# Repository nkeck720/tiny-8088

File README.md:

# tiny-8088
The Tiny 8088 KiCAD files. This exists as a mirror only. If you have issues with the board, email me at noahkeck72@gmail.com with
the subject line "8088".

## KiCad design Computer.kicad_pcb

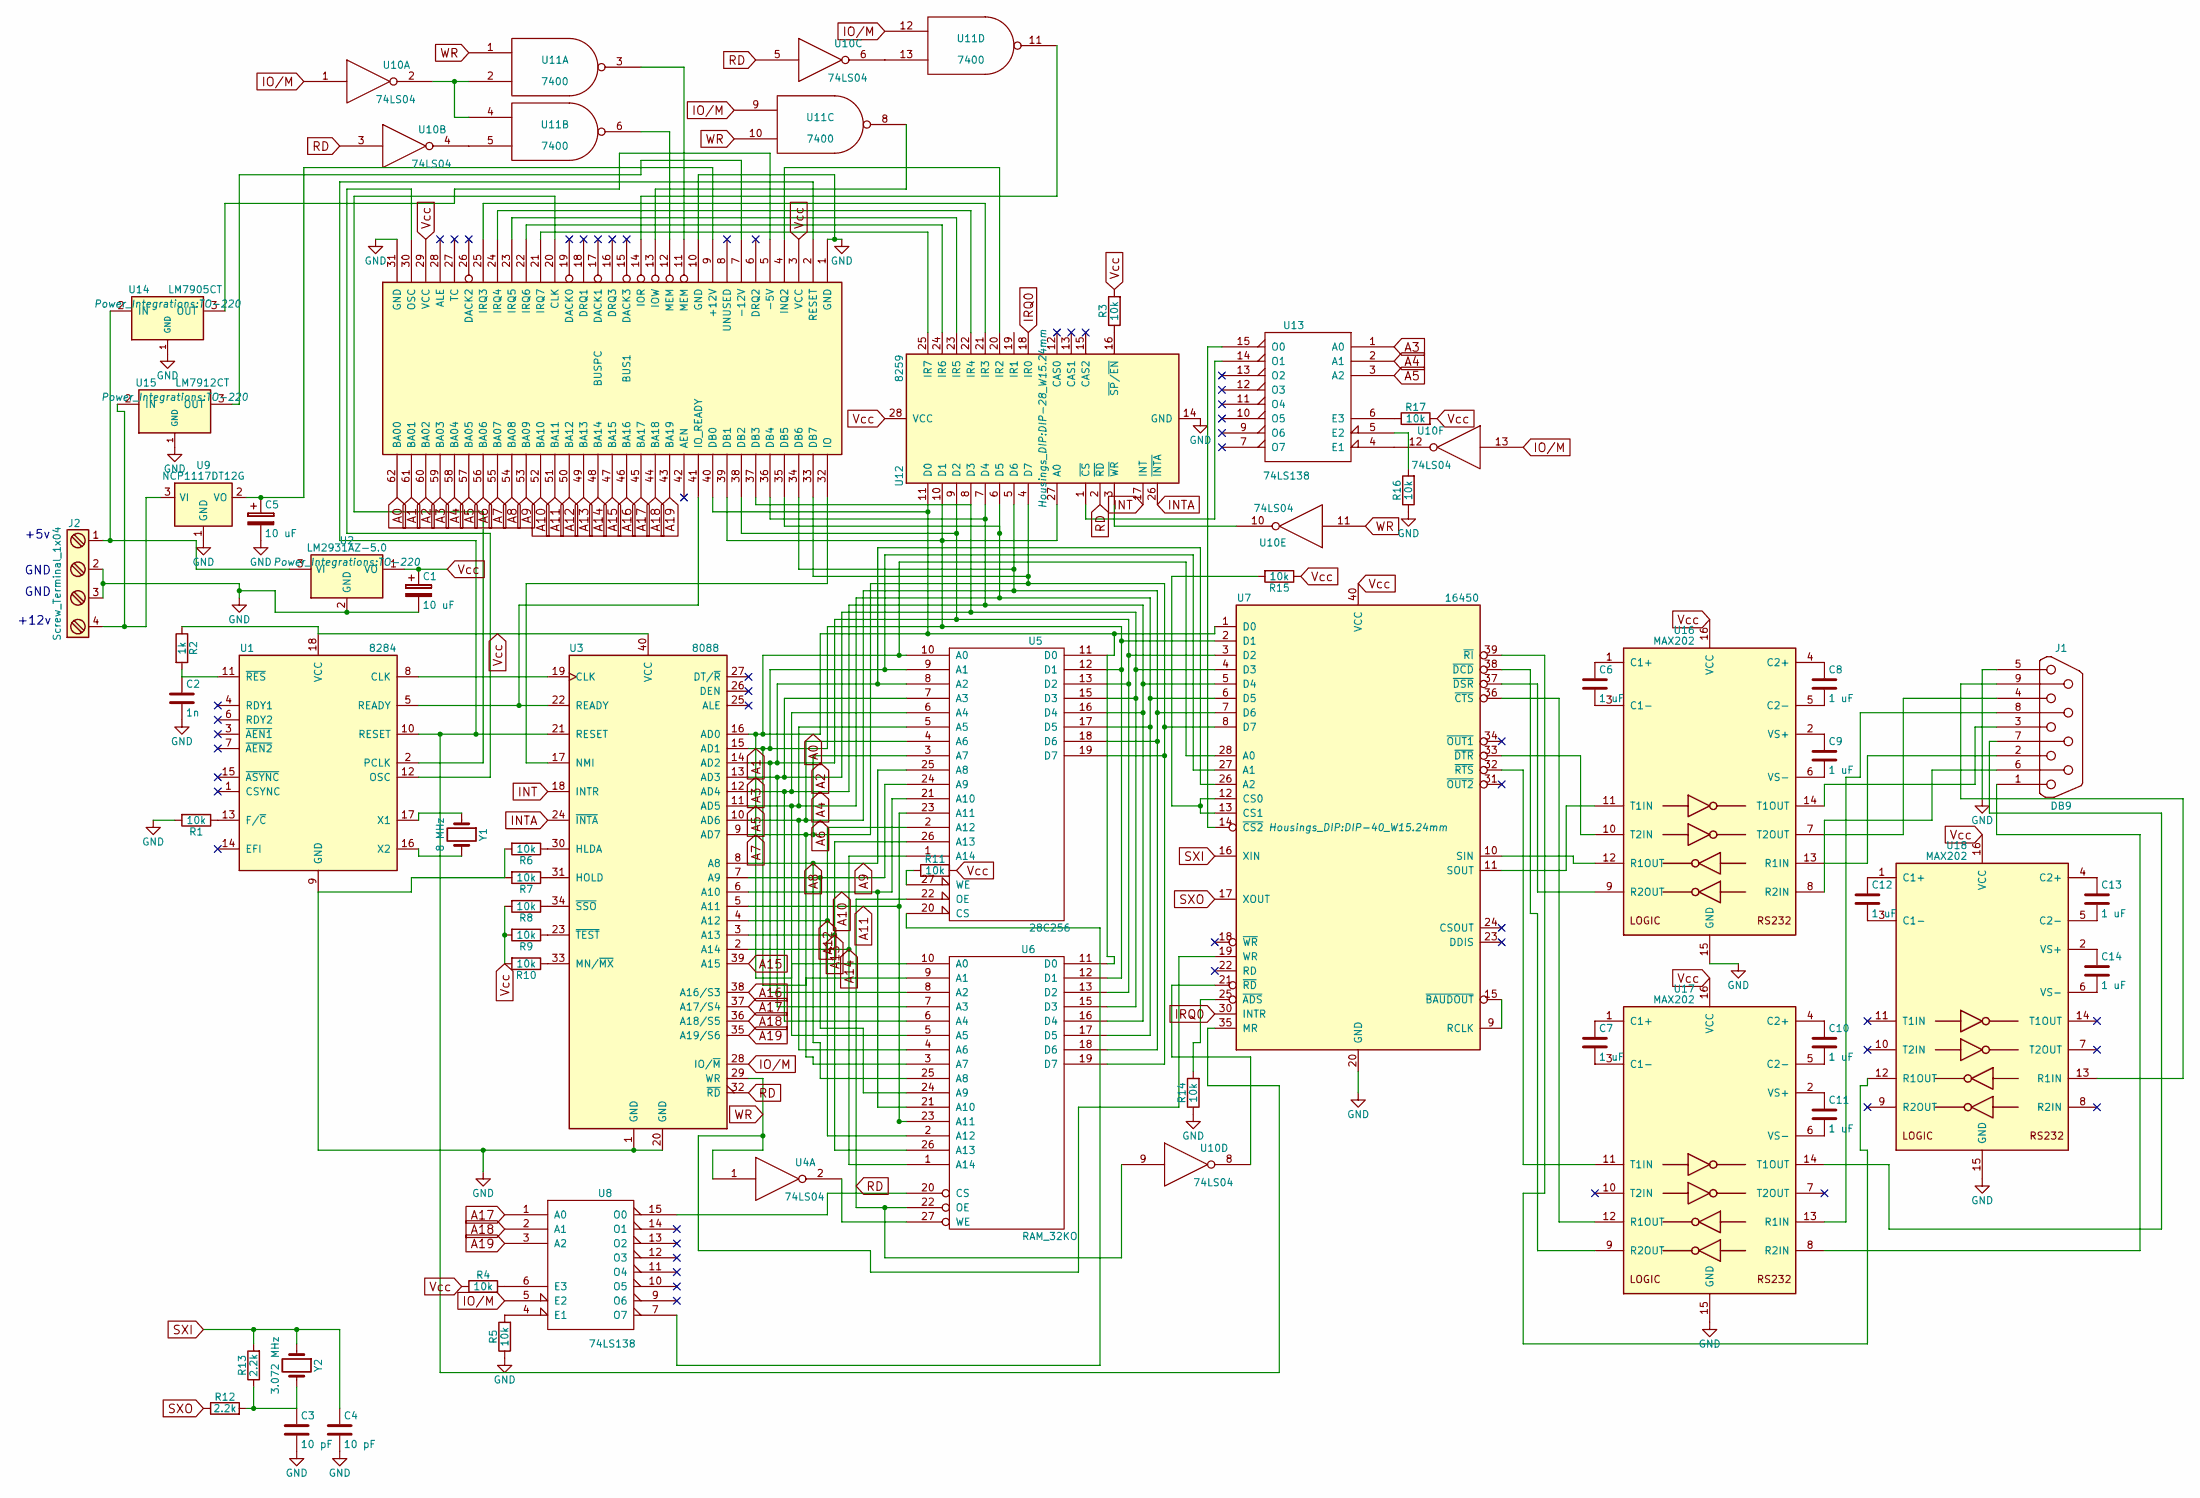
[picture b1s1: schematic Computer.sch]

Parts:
BUS1: BUSPC; ISA8
C1, C5: 10 uF; CP_Radial_D8.0mm_P3.80mm
C2: 1n; C_0603_HandSoldering
C3, C4: 10 pF; C_0603_HandSoldering
C6, C7, C8, C9, C10, C11, C12, C13, C14: 1 uF; C_0603_HandSoldering
J1: DB9; DB9FC
J2: Screw_Terminal_1x04; TerminalBlock_Pheonix_MKDS1.5-4pol
R1, R3, R4, R5, R6, R7, R8, R9, R10, R11, R14, R15, R16, R17: 10k; R_Axial_DIN0204_L3.6mm_D1.6mm_P7.62mm_Horizontal
R2: 1k; R_Axial_DIN0204_L3.6mm_D1.6mm_P7.62mm_Horizontal
R12, R13: 2.2k; R_Axial_DIN0204_L3.6mm_D1.6mm_P7.62mm_Horizontal
U1: 8284; DIP-18_W7.62mm
U2: LM2931AZ-5.0; TO-220
U3: 8088; DIP-40_W15.24mm
U4, U10: 74LS04; DIP-14_W7.62mm
U5: 28C256; DIP-28_W7.62mm
U6: RAM_32KO; DIP-28_W7.62mm
U7: 16450; DIP-40_W15.24mm
U8, U13: 74LS138; DIP-16_W7.62mm
U9: NCP1117DT12G; TO-220
U11: 7400; DIP-14_W7.62mm
U12: 8259; DIP-28_W15.24mm
U14: LM7905CT; TO-220
U15: LM7912CT; TO-220
U16, U17, U18: MAX202; DIP-16_W7.62mm
Y1: 8 MHz; Crystal_SMD_FOX_FE-2pin_7.5x5.0mm
Y2: 3.072 MHz; Crystal_SMD_FOX_FE-2pin_7.5x5.0mm

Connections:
A0: BUS1.33 (DB7), BUS1.35 (DB5), BUS1.37 (DB3), BUS1.39 (DB1), BUS1.40 (DB0), BUS1.55 (BA07), BUS1.57 (BA05), BUS1.59 (BA03), BUS1.61 (BA01), BUS1.62 (BA00), U3.9 (AD7), U3.11 (AD5), U3.13 (AD3), U3.15 (AD1), U3.16 (AD0), U5.3 (A7), U5.5 (A5), U5.7 (A3), U5.9 (A1), U5.10 (A0), U5.11 (D0), U5.12 (D1), U5.15 (D3), U5.17 (D5), U5.19 (D7), U6.3 (A7), U6.5 (A5), U6.7 (A3), U6.9 (A1), U6.10 (A0), U6.11 (D0), U6.12 (D1), U6.15 (D3), U6.17 (D5), U6.19 (D7), U7.1 (D0), U7.2 (D1), U7.4 (D3), U7.6 (D5), U7.8 (D7), U7.27 (A1), U7.28 (A0), U12.4 (D7), U12.6 (D5), U12.8 (D3), U12.10 (D1), U12.11 (D0), U12.27 (A0), U13.1 (A0), U13.3 (A2)
A2: BUS1.38 (DB2), BUS1.60 (BA02), U3.14 (AD2), U5.8 (A2), U5.13 (D2), U6.8 (A2), U6.13 (D2), U7.3 (D2), U7.26 (A2), U12.9 (D2)
A4: BUS1.36 (DB4), BUS1.58 (BA04), U3.12 (AD4), U5.6 (A4), U5.16 (D4), U6.6 (A4), U6.16 (D4), U7.5 (D4), U12.7 (D4), U13.2 (A1)
A6: BUS1.34 (DB6), BUS1.56 (BA06), U3.10 (AD6), U5.4 (A6), U5.18 (D6), U6.4 (A6), U6.18 (D6), U7.7 (D6), U12.5 (D6)
A8: BUS1.53 (BA09), BUS1.54 (BA08), U3.8 (A8), U5.25 (A8), U6.25 (A8)
A10: BUS1.52 (BA10), U3.6 (A10), U5.21 (A10), U6.21 (A10)
A11: BUS1.51 (BA11), U3.5 (A11), U5.23 (A11), U6.23 (A11)
A12: BUS1.50 (BA12), U3.4 (A12), U5.2 (A12), U6.2 (A12)
A13: BUS1.49 (BA13), U3.3 (A13), U5.26 (A13), U6.26 (A13)
A14: BUS1.48 (BA14), U3.2 (A14), U5.1 (A14), U6.1 (A14)
A15: BUS1.47 (BA15), U3.39 (A15)
A16: BUS1.46 (BA16), U3.38 (A16/S3)
A17: BUS1.45 (BA17), U3.37 (A17/S4), U8.1 (A0)
A18: BUS1.44 (BA18), U3.36 (A18/S5), U8.2 (A1)
A19: BUS1.43 (BA19), U3.35 (A19/S6), U8.3 (A2)
INT: U3.18 (INTR), U12.17 (INT)
INTA: U3.24 (~INTA~), U12.26 (~INTA~)
IO/M: U3.28 (IO/~M~), U8.5 (E2), U10.1, U10.13, U11.9, U11.12
IRQ0: U7.30 (INTR), U12.18 (IR0)
unnamed: BUS1.2 (RESET), U1.10 (RESET), U3.21 (RESET), U7.35 (MR)
unnamed: BUS1.4 (INQ2), U12.20 (IR2)
unnamed: BUS1.5 (-5V), U14.3 (OUT)
unnamed: BUS1.7 (-12V), U15.3 (OUT)
unnamed: BUS1.9 (+12V), C5.1, U9.2 (VO)
unnamed: BUS1.11 (MEM), U11.3
unnamed: BUS1.12 (MEM), U11.6
unnamed: BUS1.13 (IOW), U11.8
unnamed: BUS1.14 (IOR), U11.11
unnamed: BUS1.20 (CLK), U1.2 (PCLK)
unnamed: BUS1.21 (IRQ7), U12.25 (IR7)
unnamed: BUS1.22 (IRQ6), U12.24 (IR6)
unnamed: BUS1.23 (IRQ5), U12.23 (IR5)
unnamed: BUS1.24 (IRQ4), U12.22 (IR4)
unnamed: BUS1.25 (IRQ3), U12.21 (IR3)
unnamed: BUS1.30 (OSC), U1.12 (OSC)
unnamed: BUS1.32 (IO), U3.17 (NMI)
unnamed: BUS1.41 (IO_READY), U1.5 (READY), U3.22 (READY)
unnamed: C2.1, R2.2, U1.11 (~RES~)
unnamed: C3.1, R12.2, R13.1, Y2.2
unnamed: C6.1, U16.1 (C1+)
unnamed: C6.2, U16.3 (C1-)
unnamed: C7.1, U17.1 (C1+)
unnamed: C7.2, U17.3 (C1-)
unnamed: C8.1, U16.4 (C2+)
unnamed: C8.2, U16.5 (C2-)
unnamed: C9.1, U16.2 (VS+)
unnamed: C9.2, U16.6 (VS-)
unnamed: C10.1, U17.4 (C2+)
unnamed: C10.2, U17.5 (C2-)
unnamed: C11.1, U17.2 (VS+)
unnamed: C11.2, U17.6 (VS-)
unnamed: C12.1, U18.1 (C1+)
unnamed: C12.2, U18.3 (C1-)
unnamed: C13.1, U18.4 (C2+)
unnamed: C13.2, U18.5 (C2-)
unnamed: C14.1, U18.2 (VS+)
unnamed: C14.2, U18.6 (VS-)
unnamed: J1.1, U17.8 (R2IN)
unnamed: J1.2, U16.13 (R1IN)
unnamed: J1.3, U16.14 (T1OUT)
unnamed: J1.4, U16.7 (T2OUT)
unnamed: J1.6, U16.8 (R2IN)
unnamed: J1.7, U17.14 (T1OUT)
unnamed: J1.8, U17.13 (R1IN)
unnamed: J2.1, U2.3 (VI), U14.2 (IN)
unnamed: J2.4, U9.3 (VI), U15.2 (IN)
unnamed: R1.1, U1.13 (F/~C~)
unnamed: R3.1, U12.16 (~SP~/~EN~)
unnamed: R4.2, U8.6 (E3)
unnamed: R5.2, U8.4 (E1)
unnamed: R6.1, U3.30 (HLDA)
unnamed: R7.1, U3.31 (HOLD)
unnamed: R8.1, U3.34 (~SSO~)
unnamed: R9.1, U3.23 (~TEST~)
unnamed: R10.1, U3.33 (MN/~MX~)
unnamed: R11.1, U5.27 (WE)
unnamed: R14.2, U7.25 (~ADS~)
unnamed: R15.2, U7.12 (CS0), U7.13 (CS1)
unnamed: R16.2, U13.5 (E2)
unnamed: R17.1, U13.6 (E3)
unnamed: U1.8 (CLK), U3.19 (CLK)
unnamed: U1.16 (X2), Y1.2
unnamed: U1.17 (X1), Y1.1
unnamed: U3.7 (A9), U5.24 (A9), U6.24 (A9)
unnamed: U4.2, U6.27 (WE)
unnamed: U5.20 (CS), U8.7 (O7)
unnamed: U6.20 (CS), U8.15 (O0)
unnamed: U7.9 (RCLK), U7.15 (~BAUDOUT~)
unnamed: U10.2, U11.2, U11.4
unnamed: U10.4, U11.5
unnamed: U10.6, U11.13
unnamed: U7.21 (~RD~), U10.8
unnamed: U10.10, U12.3 (~WR~)
unnamed: U10.12, U13.4 (E1)
unnamed: U12.1 (~CS~), U13.14 (O1)
unnamed: U7.14 (~CS2~), U13.15 (O0)
unnamed: U7.37 (~DSR~), U16.9 (R2OUT)
unnamed: U7.33 (~DTR~), U16.10 (T2IN)
unnamed: U7.11 (SOUT), U16.11 (T1IN)
unnamed: U7.10 (SIN), U16.12 (R1OUT)
unnamed: U7.38 (~DCD~), U17.9 (R2OUT)
unnamed: U7.32 (~RTS~), U17.11 (T1IN)
unnamed: U7.36 (~CTS~), U17.12 (R1OUT)
unnamed: U7.39 (~RI~), U18.12 (R1OUT)
RD: U3.32 (~RD~), U5.22 (OE), U6.22 (OE), U10.3, U10.5, U10.9, U12.2 (~RD~)
SXI: C4.1, R13.2, U7.16 (XIN), Y2.1
SXO: R12.1, U7.17 (XOUT)
Vcc: BUS1.3 (VCC), BUS1.29 (VCC), C1.1, R2.1, R3.2, R4.1, R8.2, R9.2, R10.2, R11.2, R15.1, R17.2, U1.18 (VCC), U2.1 (VO), U3.40 (VCC), U4.14 (VCC), U5.28 (VCC), U6.28 (VCC), U7.40 (VCC), U8.16 (VCC), U10.14 (VCC), U11.14 (VCC), U12.28 (VCC), U13.16 (VCC), U16.16 (VCC), U17.16 (VCC), U18.16 (VCC)
WR: U3.29 (WR), U4.1, U7.19 (WR), U10.11, U11.1, U11.10

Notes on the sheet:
+5v
GND
+12v

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
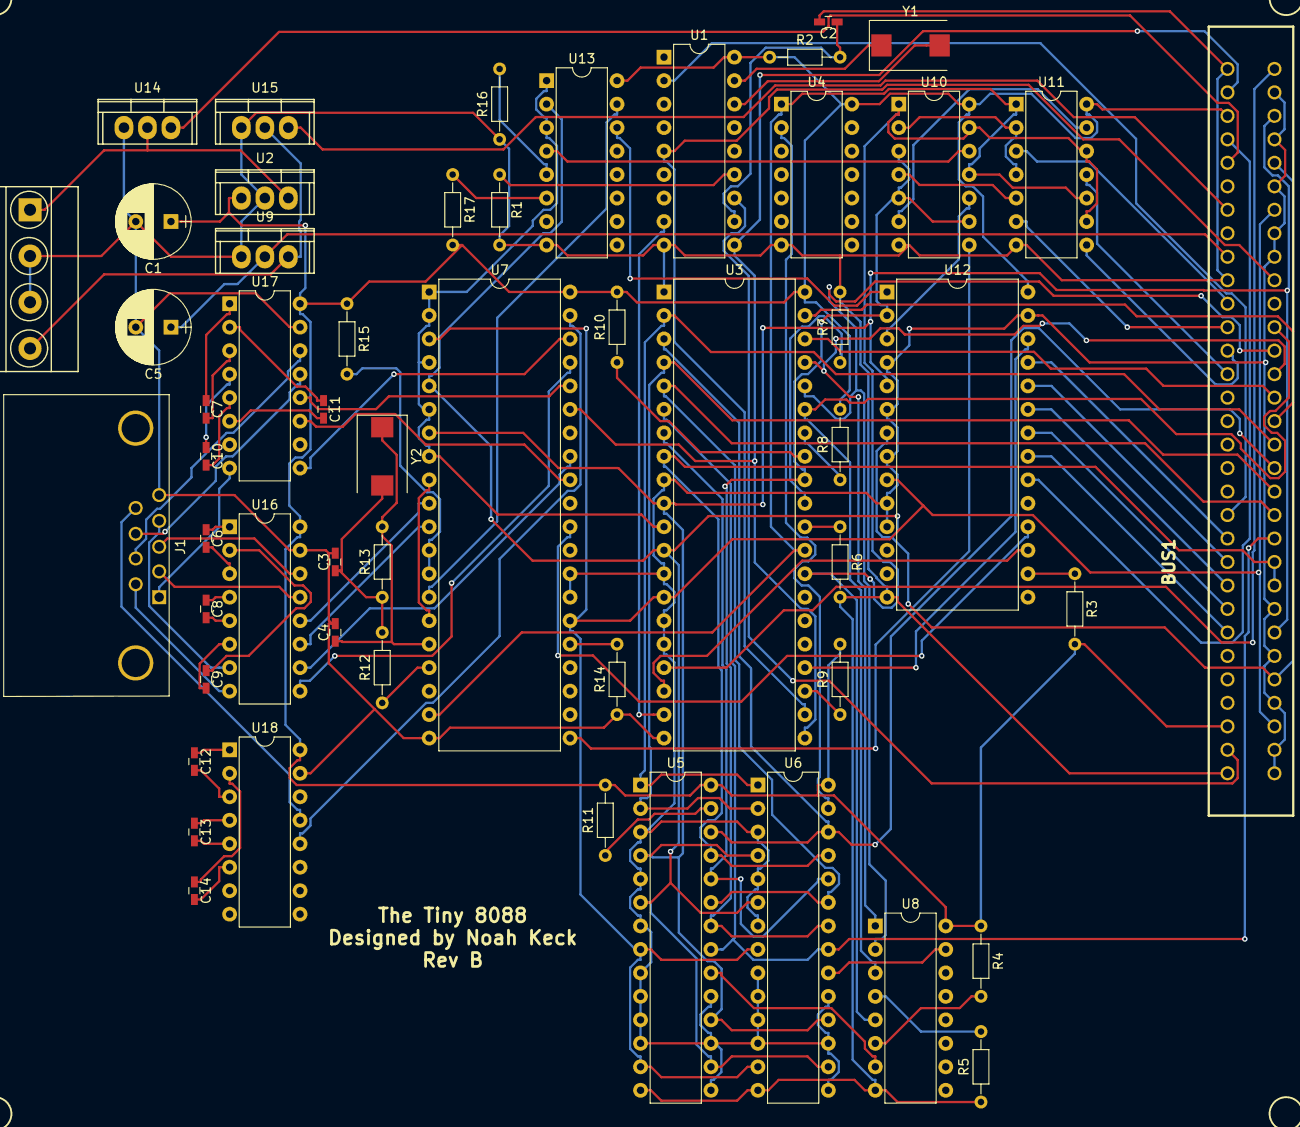
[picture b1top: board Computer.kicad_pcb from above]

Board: 2 copper layers, 54 parts (0 on the bottom side), 111 nets.

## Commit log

2017-03-12 Start repository
    Started the repository locally.
2017-03-12 Create LICENSE
2017-03-12 Delete files
    This is so that .gitignore will do its job.
2017-03-12 Fix GND fill issue
    There was an area of the copper fill on B.Cu that wasn't getting any
    connection to ground. I fixed this here.
2017-03-12 Resize schematic, add PDF
    Here I resized the schematic to A3 to fit everything and added a PDF of
    the schematic as well.
2017-03-13 Update to revision A
2017-03-14 Add -12v and -5v rails
2017-03-17 Start adding RS232 level shifters
2017-03-17 Finish level shifters
2017-03-17 Finish Rev. B
2017-03-19 Start BIOS work
2017-03-30 More BIOS work
2017-04-07 Added edge cuts
